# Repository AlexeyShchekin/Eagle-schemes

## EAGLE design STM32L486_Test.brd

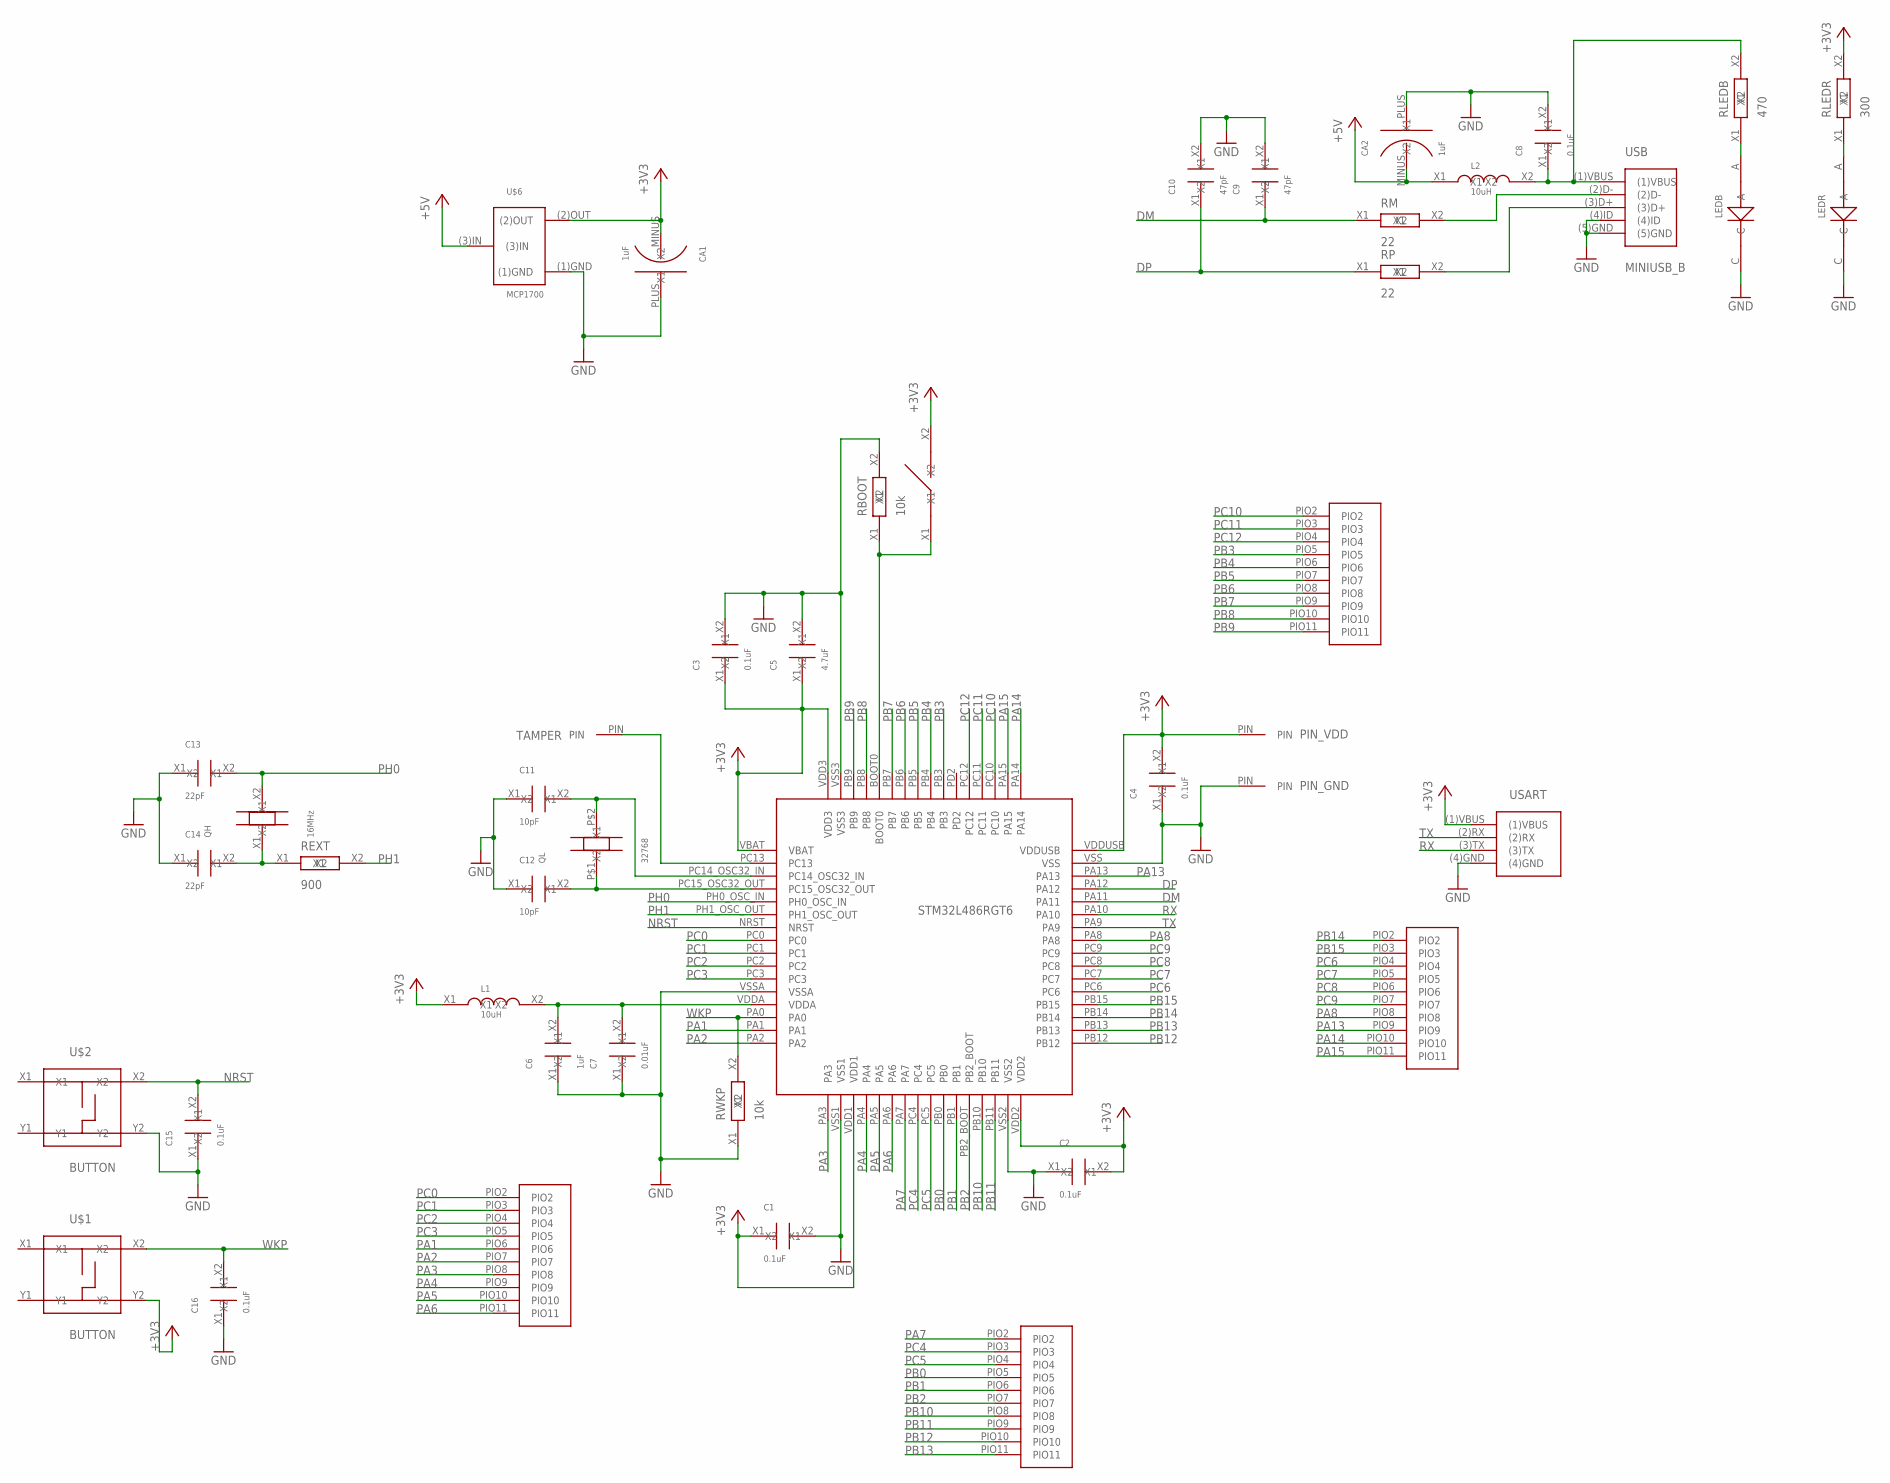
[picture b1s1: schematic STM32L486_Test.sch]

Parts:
C1, C2, C3, C4, C8, C15, C16: 0.1uF; SMD_2.1X1.25
C5: 4.7uF; SMD_2.1X1.25
C6: 1uF; SMD_2.1X1.25
C7: 0.01uF; SMD_2.1X1.25
C9, C10: 47pF; SMD_2.1X1.25
C11, C12: 10pF; SMD_2.1X1.25
C13, C14: 22pF; SMD_2.1X1.25
CA1, CA2: 1uF; C_SMD_TA_A
L1, L2: 10uH; SMD_2.1X1.25
LEDB: LED0805; SMD0805
LEDR: LED0805; SMD0805
PIN_GND: PIN
PIN_VDD: PIN
QH: 16MHz; QUARTZ_SMD
QL: 32768; QUARTZ_CYL
RBOOT: 10k; SMD_2.1X1.25
REXT: 900; SMD_2.1X1.25
RLEDB: 470; SMD_2.1X1.25
RLEDR: 300; SMD_2.1X1.25
RM: 22; SMD_2.1X1.25
RP: 22; SMD_2.1X1.25
RWKP: 10k; SMD_2.1X1.25
STM32L486RGT6: STM32L486
TAMPER: PIN
U$1, U$2: BUTTON
U$3, U$4, U$5, U$7: PIO_10
U$6: MCP1700
U$9: DIP_1
USART: USART
USB: MINIUSB_B

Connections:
+3V3: C1.X1, C2.X2, C3.X1, C4.X2, C5.X1, CA1.MINUS (X1), L1.X1, PIN_VDD.PIN, RLEDR.X2, STM32L486RGT6.VBAT, STM32L486RGT6.VDD1, STM32L486RGT6.VDD2, STM32L486RGT6.VDD3, STM32L486RGT6.VDDUSB, U$1.Y2, U$6.(2)OUT, U$9.X2, USART.(1)VBUS
+5V: CA2.MINUS (X1), L2.X1, U$6.(3)IN
DM: C9.X1, RM.X1, STM32L486RGT6.PA11
DP: C10.X1, RP.X1, STM32L486RGT6.PA12
GND: C1.X2, C2.X1, C3.X2, C4.X1, C5.X2, C6.X1, C7.X1, C8.X2, C9.X2, C10.X2, C11.X1, C12.X1, C13.X1, C14.X1, C15.X1, C16.X1, CA1.PLUS (X2), CA2.PLUS (X2), LEDB.C, LEDR.C, PIN_GND.PIN, RBOOT.X2, RWKP.X1, STM32L486RGT6.VSS, STM32L486RGT6.VSS1, STM32L486RGT6.VSS2, STM32L486RGT6.VSS3, STM32L486RGT6.VSSA, U$2.Y2, U$6.(1)GND, USART.(4)GND, USB.(4)ID, USB.(5)GND
unnamed: RBOOT.X1, STM32L486RGT6.BOOT0, U$9.X1
unnamed: C11.X2, QL.P$2 (X2), STM32L486RGT6.PC14_OSC32_IN
unnamed: LEDB.A, RLEDB.X1
unnamed: C8.X1, L2.X2, RLEDB.X2, USB.(1)VBUS
unnamed: RM.X2, USB.(2)D-
unnamed: RP.X2, USB.(3)D+
unnamed: LEDR.A, RLEDR.X1
unnamed: C12.X2, QL.P$1 (X1), STM32L486RGT6.PC15_OSC32_OUT
unnamed: STM32L486RGT6.PC13, TAMPER.PIN
unnamed: C14.X2, QH.X1, REXT.X1
NRST: C15.X2, STM32L486RGT6.NRST, U$2.X2
PA1: STM32L486RGT6.PA1, U$3.PIO6
PA2: STM32L486RGT6.PA2, U$3.PIO7
PA3: STM32L486RGT6.PA3, U$3.PIO8
PA4: STM32L486RGT6.PA4, U$3.PIO9
PA5: STM32L486RGT6.PA5, U$3.PIO10
PA6: STM32L486RGT6.PA6, U$3.PIO11
PA7: STM32L486RGT6.PA7, U$4.PIO2
PA8: STM32L486RGT6.PA8, U$5.PIO8
PA13: STM32L486RGT6.PA13, U$5.PIO9
PA14: STM32L486RGT6.PA14, U$5.PIO10
PA15: STM32L486RGT6.PA15, U$5.PIO11
PB0: STM32L486RGT6.PB0, U$4.PIO5
PB1: STM32L486RGT6.PB1, U$4.PIO6
PB2: STM32L486RGT6.PB2_BOOT, U$4.PIO7
PB3: STM32L486RGT6.PB3, U$7.PIO5
PB4: STM32L486RGT6.PB4, U$7.PIO6
PB5: STM32L486RGT6.PB5, U$7.PIO7
PB6: STM32L486RGT6.PB6, U$7.PIO8
PB7: STM32L486RGT6.PB7, U$7.PIO9
PB8: STM32L486RGT6.PB8, U$7.PIO10
PB9: STM32L486RGT6.PB9, U$7.PIO11
PB10: STM32L486RGT6.PB10, U$4.PIO8
PB11: STM32L486RGT6.PB11, U$4.PIO9
PB12: STM32L486RGT6.PB12, U$4.PIO10
PB13: STM32L486RGT6.PB13, U$4.PIO11
PB14: STM32L486RGT6.PB14, U$5.PIO2
PB15: STM32L486RGT6.PB15, U$5.PIO3
PC0: STM32L486RGT6.PC0, U$3.PIO2
PC1: STM32L486RGT6.PC1, U$3.PIO3
PC2: STM32L486RGT6.PC2, U$3.PIO4
PC3: STM32L486RGT6.PC3, U$3.PIO5
PC4: STM32L486RGT6.PC4, U$4.PIO3
PC5: STM32L486RGT6.PC5, U$4.PIO4
PC6: STM32L486RGT6.PC6, U$5.PIO4
PC7: STM32L486RGT6.PC7, U$5.PIO5
PC8: STM32L486RGT6.PC8, U$5.PIO6
PC9: STM32L486RGT6.PC9, U$5.PIO7
PC10: STM32L486RGT6.PC10, U$7.PIO2
PC11: STM32L486RGT6.PC11, U$7.PIO3
PC12: STM32L486RGT6.PC12, U$7.PIO4
PH0: C13.X2, QH.X2, STM32L486RGT6.PH0_OSC_IN
PH1: REXT.X2, STM32L486RGT6.PH1_OSC_OUT
RX: STM32L486RGT6.PA10, USART.(3)TX
TX: STM32L486RGT6.PA9, USART.(2)RX
VDDA: C6.X2, C7.X2, L1.X2, STM32L486RGT6.VDDA
WKP: C16.X2, RWKP.X2, STM32L486RGT6.PA0, U$1.X2

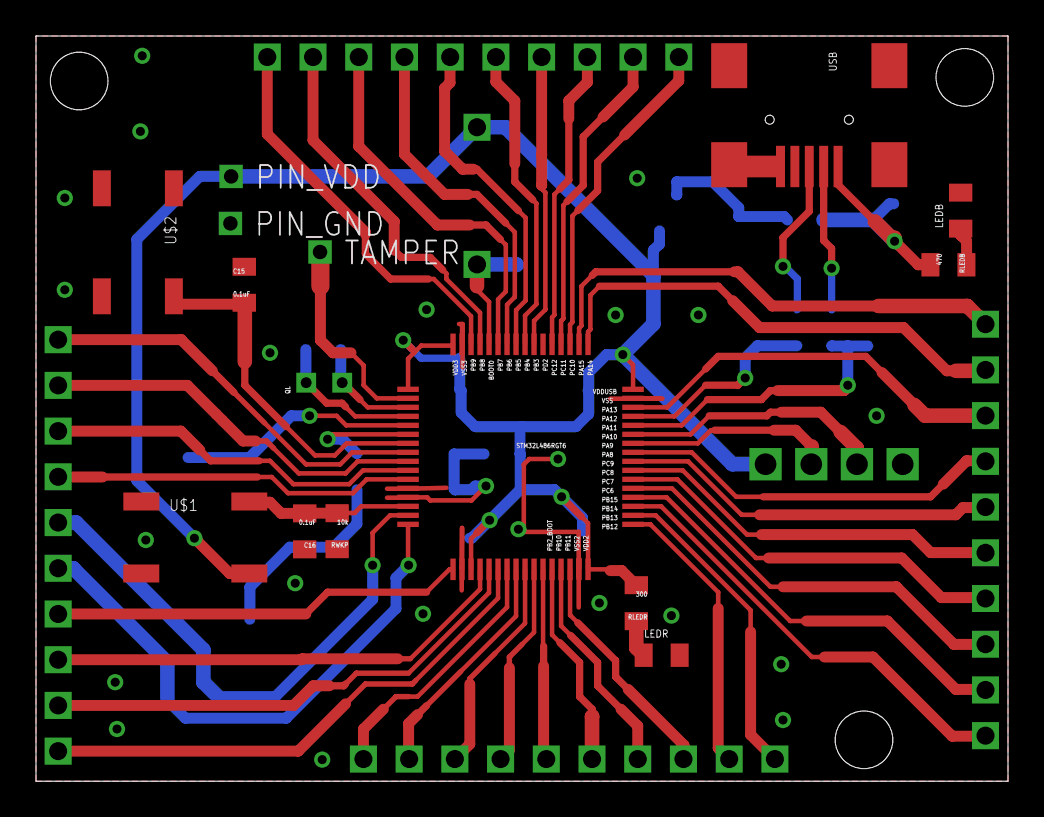
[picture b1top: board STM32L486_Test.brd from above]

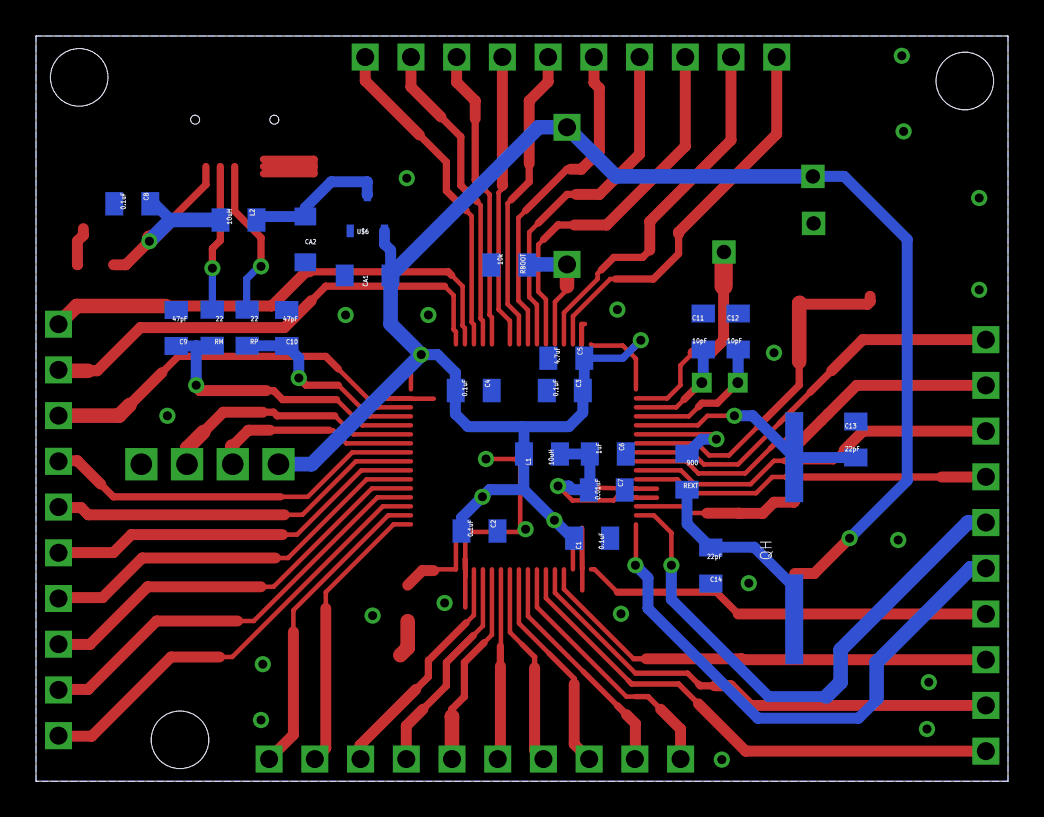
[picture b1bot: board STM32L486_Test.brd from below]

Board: 2 copper layers, 54.0 x 41.4 mm, 45 parts (24 on the bottom side), 62 nets.

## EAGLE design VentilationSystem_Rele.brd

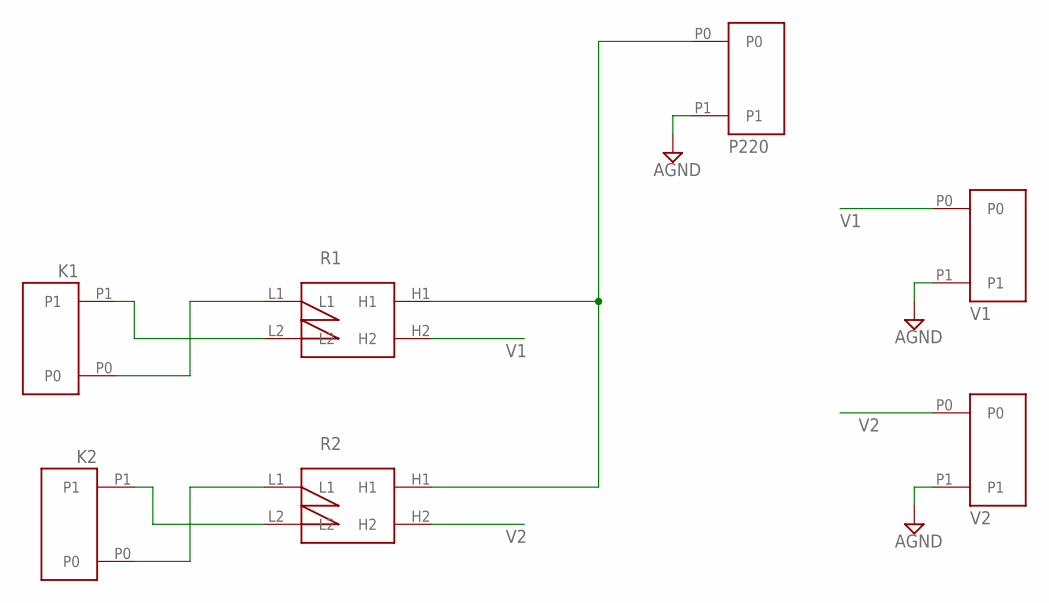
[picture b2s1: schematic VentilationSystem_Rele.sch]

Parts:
K1, K2: RAIL_2
P220: RAIL_2
R1, R2: NPR-RELE
V1, V2: RAIL_2

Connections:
AGND: P220.P1, V1.P1, V2.P1
unnamed: K2.P1, R2.L2
unnamed: K1.P0, R1.L1
unnamed: K1.P1, R1.L2
unnamed: K2.P0, R2.L1
unnamed: P220.P0, R1.H1, R2.H1
V1: R1.H2, V1.P0
V2: R2.H2, V2.P0

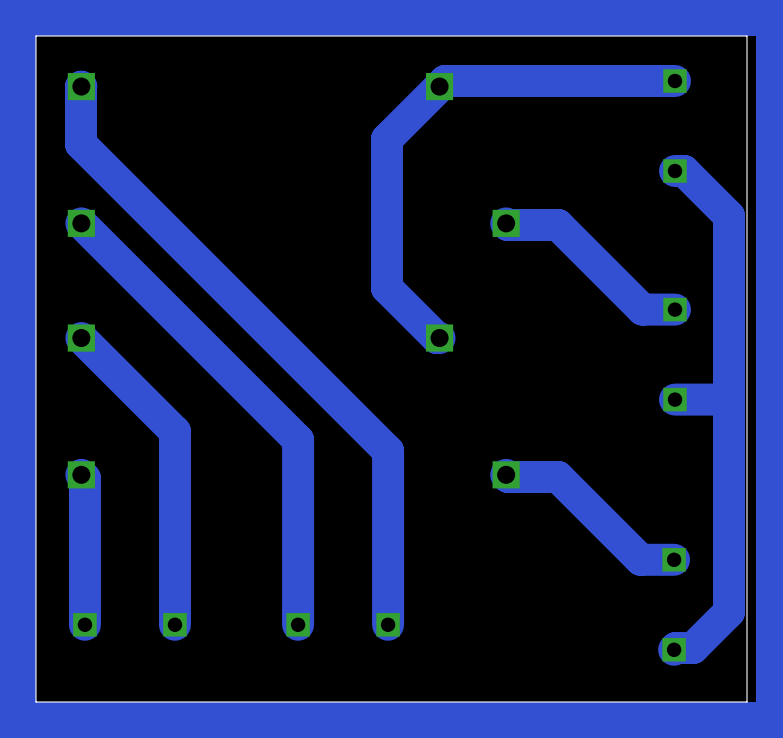
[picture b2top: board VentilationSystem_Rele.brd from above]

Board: 2 copper layers, 39.5 x 37.0 mm, 7 parts (0 on the bottom side), 8 nets.

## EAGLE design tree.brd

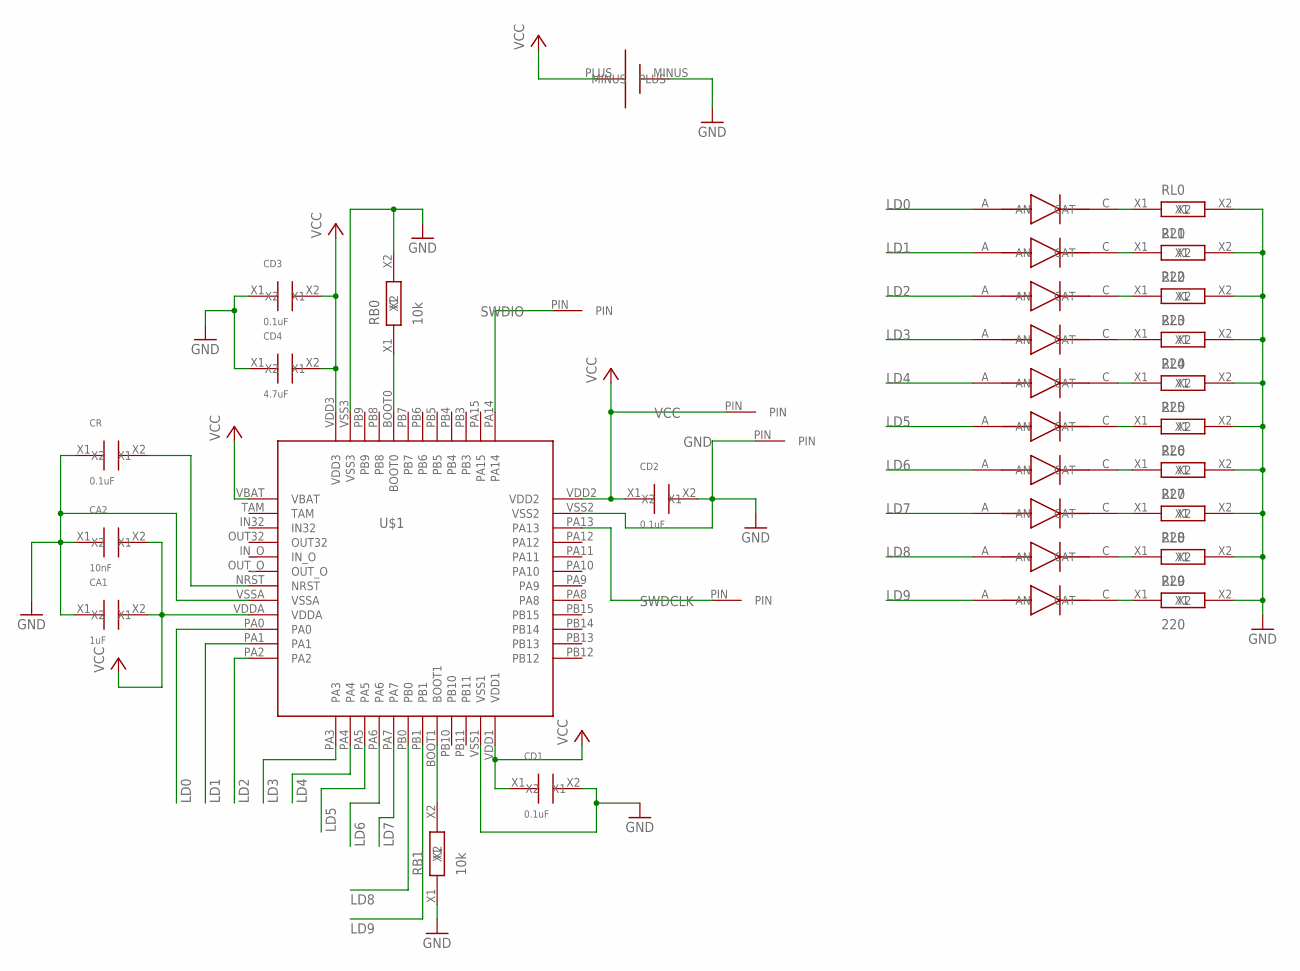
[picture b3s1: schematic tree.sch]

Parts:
CA1: 1uF; SMD_2.1X1.25
CA2: 10nF; SMD_2.1X1.25
CD1, CD2, CD3: 0.1uF; SMD_2.1X1.25
CD4: 4.7uF; SMD_2.1X1.25
CR: 0.1uF; SMD_2.1X1.25
GND: PIN_06
RB0, RB1: 10k; SMD_2.1X1.25
RL0, RL1, RL2, RL3, RL4, RL5, RL6, RL7, RL8, RL9: 220; SMD_2.1X1.25
SWDCLK: PIN_06
SWDIO: PIN_06
U$1: STM32F103CBT6
U$2, U$3, U$4, U$5, U$6, U$7, U$8, U$9, U$10, U$11: LED0805
U$12: VBAT
VCC: PIN_06

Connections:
GND: CA1.X1, CA2.X1, CD1.X2, CD2.X2, CD3.X1, CD4.X1, CR.X1, GND.PIN, RB0.X2, RB1.X1, RL0.X2, RL1.X2, RL2.X2, RL3.X2, RL4.X2, RL5.X2, RL6.X2, RL7.X2, RL8.X2, RL9.X2, U$1.VSS1, U$1.VSS2, U$1.VSS3, U$1.VSSA, U$12.MINUS
LD0: U$1.PA0, U$4.A (AN)
LD1: U$1.PA1, U$2.A (AN)
LD2: U$1.PA2, U$3.A (AN)
LD3: U$1.PA3, U$5.A (AN)
LD4: U$1.PA4, U$6.A (AN)
LD5: U$1.PA5, U$7.A (AN)
LD6: U$1.PA6, U$8.A (AN)
LD7: U$1.PA7, U$9.A (AN)
LD8: U$1.PB0, U$10.A (AN)
LD9: U$1.PB1, U$11.A (AN)
unnamed: RB1.X2, U$1.BOOT1
unnamed: CR.X2, U$1.NRST
unnamed: RB0.X1, U$1.BOOT0
unnamed: RL0.X1, U$4.C (CAT)
unnamed: RL1.X1, U$2.C (CAT)
unnamed: RL2.X1, U$3.C (CAT)
unnamed: RL3.X1, U$5.C (CAT)
unnamed: RL4.X1, U$6.C (CAT)
unnamed: RL5.X1, U$7.C (CAT)
unnamed: RL6.X1, U$8.C (CAT)
unnamed: RL7.X1, U$9.C (CAT)
unnamed: RL8.X1, U$10.C (CAT)
unnamed: RL9.X1, U$11.C (CAT)
SWDCLK: SWDCLK.PIN, U$1.PA13
SWDIO: SWDIO.PIN, U$1.PA14
VCC: CA1.X2, CA2.X2, CD1.X1, CD2.X1, CD3.X2, CD4.X2, U$1.VBAT, U$1.VDD1, U$1.VDD2, U$1.VDD3, U$1.VDDA, U$12.PLUS, VCC.PIN

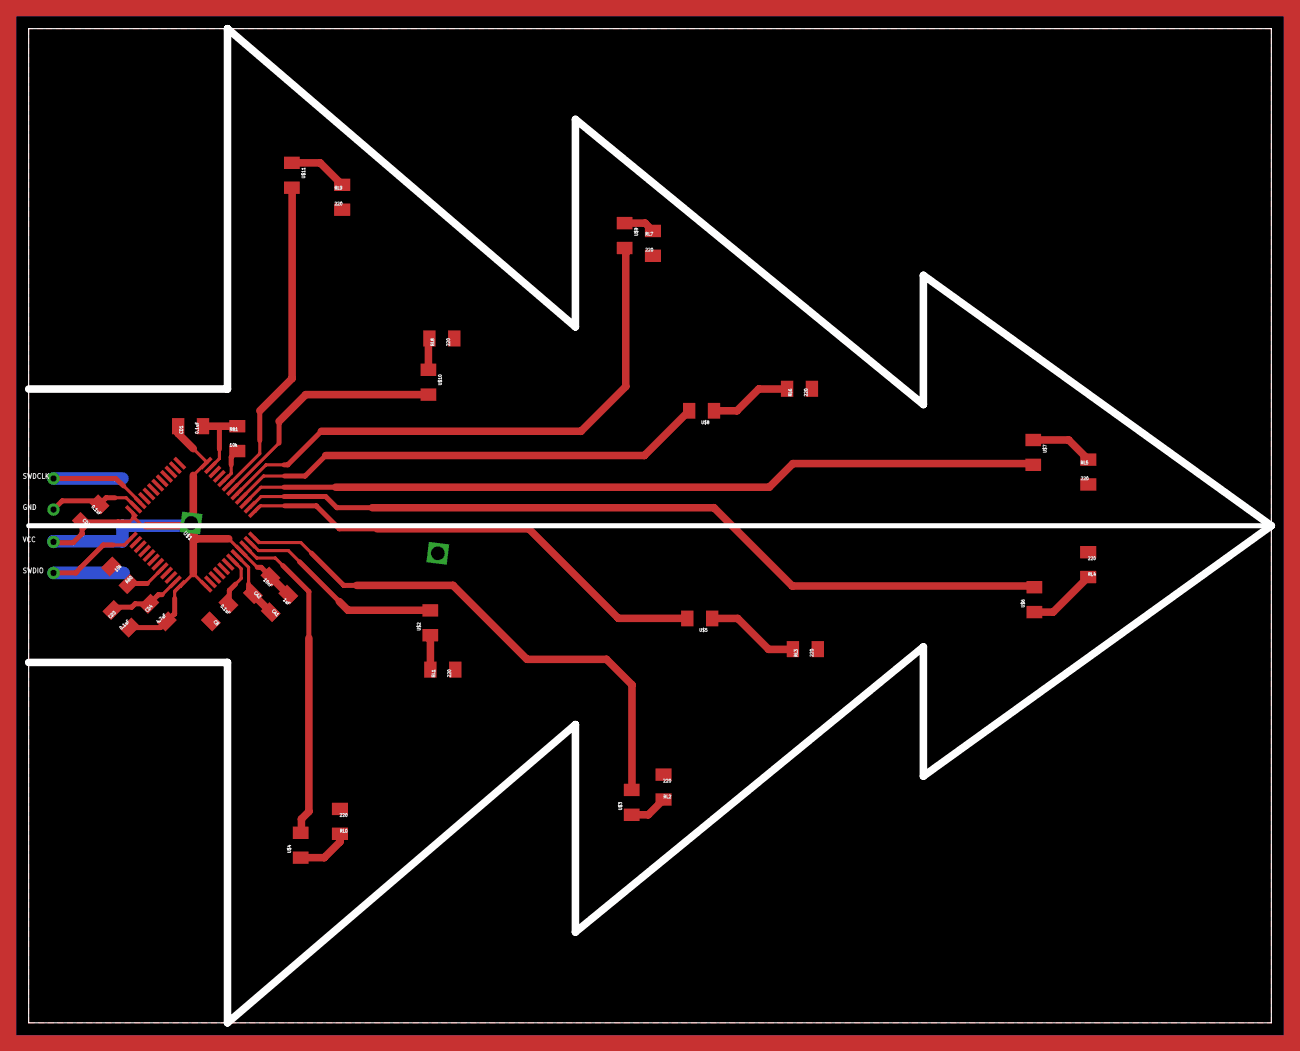
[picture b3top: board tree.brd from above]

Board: 2 copper layers, 100.0 x 80.0 mm, 35 parts (0 on the bottom side), 27 nets.
